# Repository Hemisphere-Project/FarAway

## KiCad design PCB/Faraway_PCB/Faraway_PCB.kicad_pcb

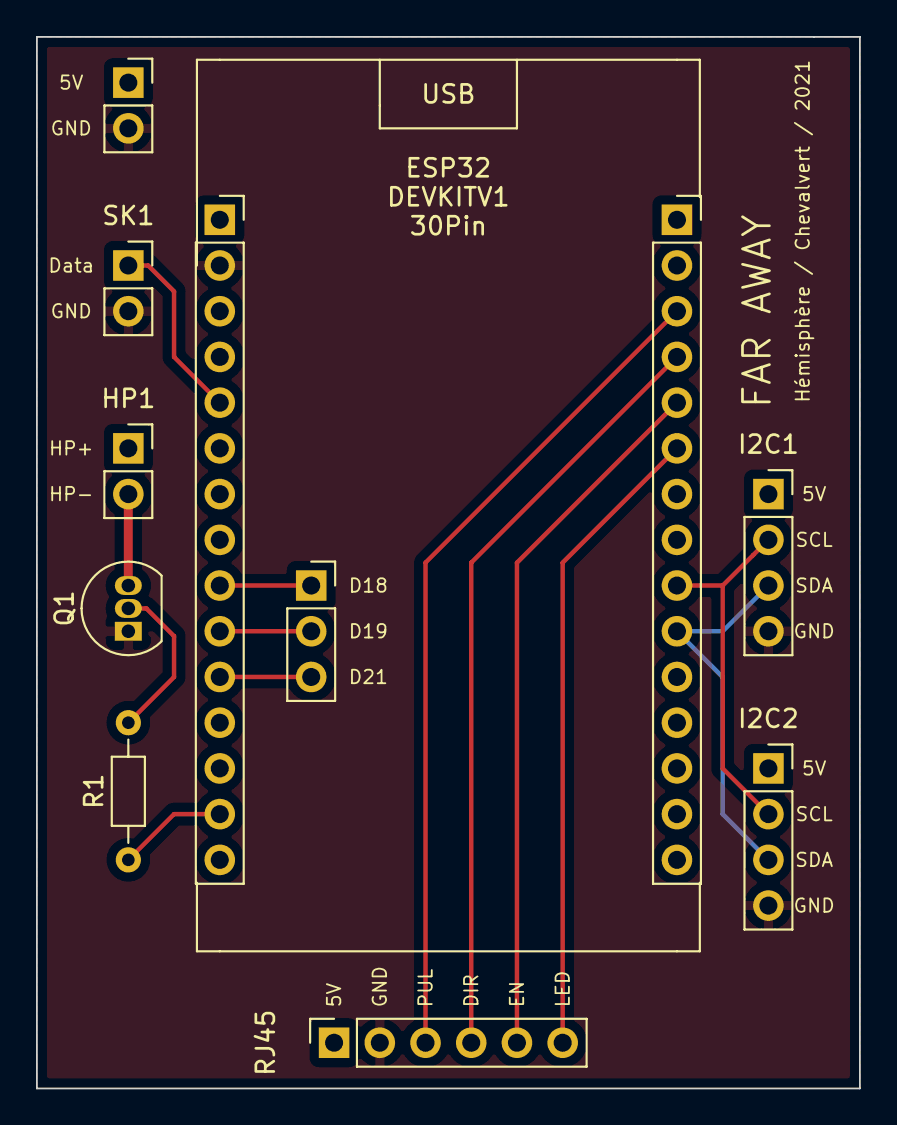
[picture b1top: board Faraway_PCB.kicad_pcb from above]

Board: 2 copper layers, 45.7 x 58.4 mm, 11 parts (0 on the bottom side), 15 nets.

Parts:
5V_BONUS1: Conn_01x02_Female; PinSocket_1x02_P2.54mm_Vertical
HP1: Conn_01x02_Female; PinSocket_1x02_P2.54mm_Vertical
I2C1, I2C2: Conn_01x04_Female; PinSocket_1x04_P2.54mm_Vertical
J1: ESP32_DevKitV1_30PIN_Left; PinSocket_1x15_P2.54mm_Vertical
J2: ESP32_DevKitV1_30PIN_Right; PinSocket_1x15_P2.54mm_Vertical
Q1: PN2222A; TO-92_Inline
R1: 1k; R_Axial_DIN0204_L3.6mm_D1.6mm_P7.62mm_Horizontal
RJ45_INPUT1: Conn_01x06_Female; PinSocket_1x06_P2.54mm_Vertical
SK1: Conn_01x02_Female; PinSocket_1x02_P2.54mm_Vertical
SPARE_PINS1: Conn_01x03_Female; PinSocket_1x03_P2.54mm_Vertical

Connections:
+5V: 5V_BONUS1.1, HP1.1, I2C1.1, I2C2.1, J2.1, RJ45_INPUT1.1
AUDIO: J1.14, R1.1
DIR: J2.4, RJ45_INPUT1.4
EN: J2.5, RJ45_INPUT1.5
GND: 5V_BONUS1.2, I2C1.4, I2C2.4, J1.2, Q1.1, RJ45_INPUT1.2, SK1.2
LED: J2.6, RJ45_INPUT1.6
unnamed: HP1.2, Q1.3
unnamed: J1.9, SPARE_PINS1.1
unnamed: J1.10, SPARE_PINS1.2
unnamed: J1.11, SPARE_PINS1.3
unnamed: Q1.2, R1.2
PUL: J2.3, RJ45_INPUT1.3
SCL: I2C1.2, I2C2.2, J2.9
SDA: I2C1.3, I2C2.3, J2.10
SK: J1.5, SK1.1

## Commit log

2021-01-19 init
2021-01-27 Lidar tests
2021-02-02 Create Acceleration_theorique_FarAway.pde
    Ajout fichier simulation
2021-02-03 3D v1 ok
2021-02-03 actu
2021-02-03 motor nema dimensions
2021-02-03 folder p5
2021-02-10 Create Far away - Devis piece usinage.pdf
    Ajout plan devis usinage
2021-02-15 plan v1.1
2021-02-22 rgbw
2021-03-10 motor ok & ota
2021-03-10 proto atom
2021-03-10 Full test with K32-lib lite
2021-03-10 base sketch chaser
2021-03-11 rgbw power test
2021-03-11 boites
2021-03-11 code ready to test
2021-03-11 remote debug
2021-03-12 Dev SpeedyStepper test
2021-03-17 Dev multiple
2021-03-18 v1.4 - new platine + goussets
2021-03-18 boite?
2021-03-18 Final frontier
2021-03-31 cleanup proto
2021-04-02 laser ok
2021-04-06 laser update
2021-04-08 pcb start
2021-04-08 new exports
2021-04-09 pcb ok
2021-04-09 pcb gbr
2021-04-13 Create Far away - Plan.dwg
    Ajout plan de coupe
2021-04-13 update plan _ prod OK
2021-04-16 plan v2
2021-04-19 ESP32 version PCB
2021-04-19 pinout
2021-04-21 cablage ok
2021-04-21 folder
2021-05-11 Full audio
2021-05-20 update plans
2021-05-26 wednesday
2021-05-27 perçages
2021-05-27 trous manchonnage
2021-06-09 metz
2021-08-05 metz aout watchdog
2021-09-29 Casing
2021-12-16 case
2022-01-28 remove hello_world
2022-01-28 anim led loader
2022-02-03 reddot
2022-10-17 CleanUP and change WDT instead of ESP.Reboot
2022-10-24 fix ota watchdog
2025-01-16 pio version + lower accel on id=6
2025-01-16 slow accel for id 6
2025-01-16 fix id=6
2025-01-22 fix flexy-core
2025-01-22 ota with confirm
2025-01-22 version
2025-10-23 14: fix blink (not efficient -> need booster !)
2025-10-27 spiffs format / remove iram
